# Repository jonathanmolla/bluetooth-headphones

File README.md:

# Bluetooth Headphones

Custom Bluetooth headphone electronics by **Jonathan Molla**, bringing together stereo audio circuit design, PCB layout, battery charging, STM32 controller configuration, and LTspice simulation.

## Main audio PCB

[Main audio PCB source](hardware/main/) · [Audio and controller schematics](docs/schematics/main/)

## Charging and power PCB

[Charging and power PCB source](hardware/power/) · [Charging circuit schematic](docs/schematics/power/Charging%20and%20Power.svg)

## Project at a glance

| Area | Implementation in this repository |
| --- | --- |
| Bluetooth audio | Microchip BM83 module in the KiCad audio schematic |
| Headphone amplifier | TI TPA6130A2, with AC-coupled analog inputs |
| Controller | STM32U031C8T6 firmware, BM83 UART, amplifier control, and battery monitoring |
| Charging | MCP73833 circuit on a separate power PCB |
| Battery / drivers | SparkFun PRT-13851 protected 400 mAh pack; Ole Wolff OWR-4009T-38E, nominal 38 ohm |
| BM83 programming | Separate single-PCB spring-contact fixture, revision C |
| Regulation | TPS7A2030PDBVR, fixed 3.0 V regulator |
| Design tools | KiCad, STM32CubeMX, LTspice |
| Simulation scope | Simplified analog coupling and voltage-gain models |

## Explore the project

| What you want to see | Where to find it |
| --- | --- |
| **PCB layouts and editable board files** | [Main audio PCB](hardware/main/#main-audio-pcb) · [Charging and power PCB](hardware/power/#charging-and-power-pcb) |
| **Schematics** | [Audio, controller, and charging circuit diagrams](docs/schematics/) |
| **Board images** | [Main audio and power board previews](docs/images/) |
| **Circuit design and component choices** | [Architecture and design decisions](docs/design.md) |
| **STM32 firmware** | [CubeIDE project, CubeMX configuration, and build instructions](firmware/) |
| **Audio simulation** | [LTspice circuit, models, and run instructions](simulation/) |
| **Component lists** | [Main audio board BOM](hardware/main/bom.csv) · [Power board BOM](hardware/power/bom.csv) |
| **Engineering checks** | [Schematic and PCB check results](docs/validation.md) |
| **Opening the design files** | [Software and setup guide](docs/getting-started.md) |
| **Design deliverables** | [Project file guide](docs/roadmap.md) |

## System architecture

```mermaid
flowchart LR
    BT[Bluetooth source] --> BM[BM83 module]
    BM --> AC[AC coupling]
    AC --> AMP[TPA6130A2 amplifier]
    AMP --> HP[Left and right headphone drivers]
    USB[USB power input] --> CHG[MCP73833 charging circuit]
    CHG <--> BAT[Single-cell battery]
    BAT --> RAIL[VBAT rail]
    RAIL --> BM
    RAIL --> AMP
    RAIL --> LDO[TPS7A20 3.0 V regulator]
    LDO --> MCU[STM32U031 controller]
    BTN[Buttons] --> MCU
    MCU -. control interfaces .-> BM
    MCU -. I2C control .-> AMP
```

This is an architectural overview. Exact connections and component values are defined by the native schematics. The main/audio board and charging/power board are separate KiCad projects.

## Engineering highlights

- Hierarchical schematic organization for audio and MCU controls.
- A separate charging and regulation PCB.
- Project-local symbols and footprints alongside the native KiCad files.
- Stereo AC-coupling analysis with parameterized input resistance, gain, and driver loads.
- STM32 pin and peripheral configuration captured in a reproducible `.ioc` file.
- Recorded KiCad electrical and design-rule checks with a structured measurement procedure.

## Repository layout

```text
hardware/
  main/          Main audio PCB, audio and controller schematics, local libraries
  power/         Charging and power PCB, schematic and local libraries
  programmer/    Single-PCB BM83 fixture, probe footprints and assembly instructions
firmware/        STM32CubeIDE project and CubeMX controller configuration
simulation/      LTspice audio circuit, symbols, models and instructions
docs/
  images/        PCB layout previews
  schematics/    Browser-readable schematic exports
  checks/        Recorded KiCad design checks
```

## Author and references

Project owner: [Jonathan Molla](https://github.com/jonathanmolla).

See [references and third-party materials](docs/references.md) for component sources and [reuse information](NOTICE.md) before reusing the files.

[BM83 programmer source and instructions](hardware/programmer/) · [Latest design review](docs/design-review-2026-11-14.md)

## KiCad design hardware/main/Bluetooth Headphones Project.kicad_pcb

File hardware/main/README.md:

# Main audio board

This board brings together BM83 Bluetooth audio, the TPA6130A2 headphone amplifier, and the STM32 controller and button circuitry.

## Main audio PCB

**Editable board layout:** [Bluetooth Headphones Project.kicad_pcb](Bluetooth%20Headphones%20Project.kicad_pcb)

**Open the complete KiCad project:** [Bluetooth Headphones Project.kicad_pro](Bluetooth%20Headphones%20Project.kicad_pro)

**View the layout in your browser:** [Main audio PCB preview](../../docs/images/main-board.svg)

## Schematics and component list

| File | Contents |
| --- | --- |
| [Root schematic](Bluetooth%20Headphones%20Project.kicad_sch) | Project hierarchy linking the audio and controller sheets |
| [Audio schematic](Bluetooth_Audio.kicad_sch) | BM83 module, AC coupling, TPA6130A2 amplifier and headphone outputs |
| [Controller schematic](MCU_Buttons.kicad_sch) | STM32 controller and button connections |
| [Component list](bom.csv) | Schematic references, values, footprints and datasheet links |

[View all schematic previews](../../docs/schematics/) · [Open the separate charging and power board](../power/)

## Library files

`Project_Audio.pretty/` and `STM32.pretty/` contain project-local footprints. The `.kicad_sym` files contain project-local symbols. Keep these folders and both library tables beside the project when downloading it.

## November 14 review

[Cross-board circuit and layout review](../../docs/design-review-2026-11-14.md) records component values, inter-board pinout, battery/driver selection and reference-design comparisons. The CSV lists schematic parts; the existing Google document remains the purchasing BOM.

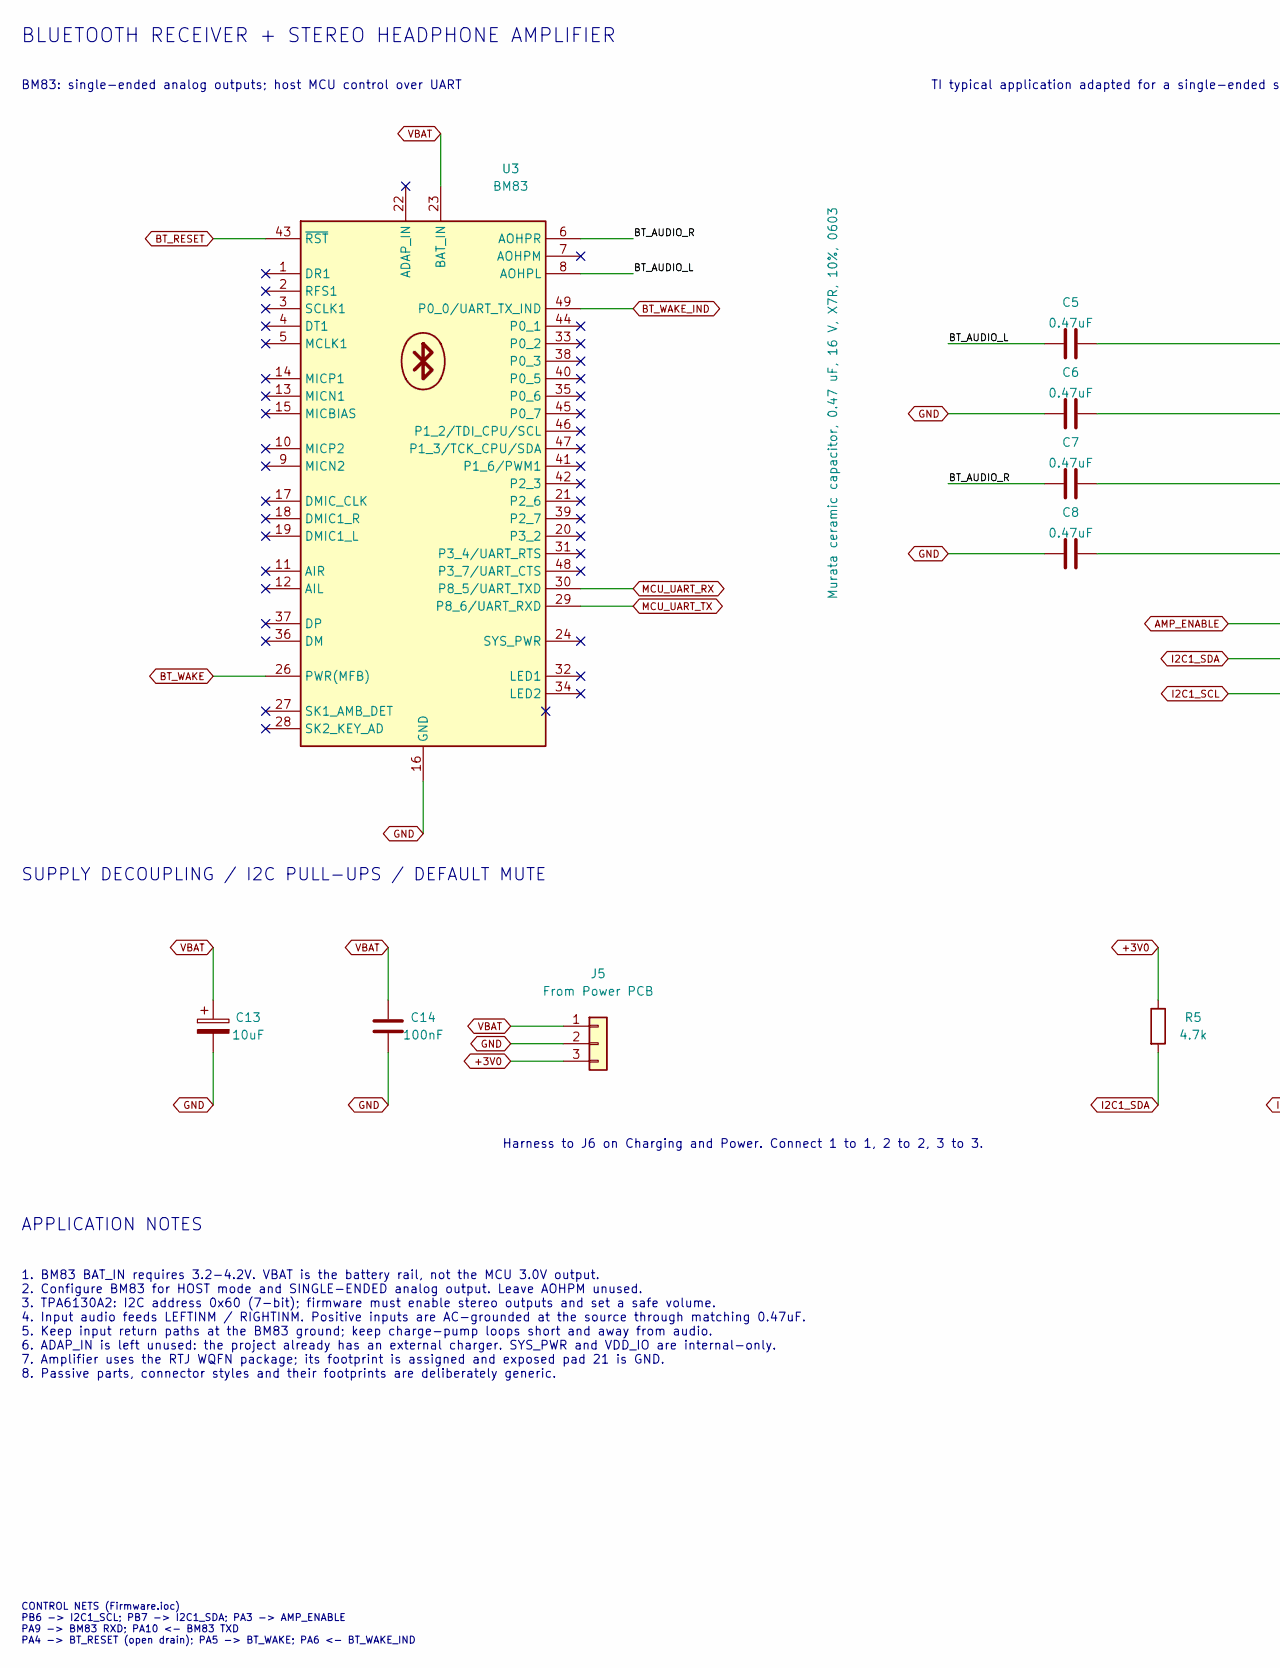
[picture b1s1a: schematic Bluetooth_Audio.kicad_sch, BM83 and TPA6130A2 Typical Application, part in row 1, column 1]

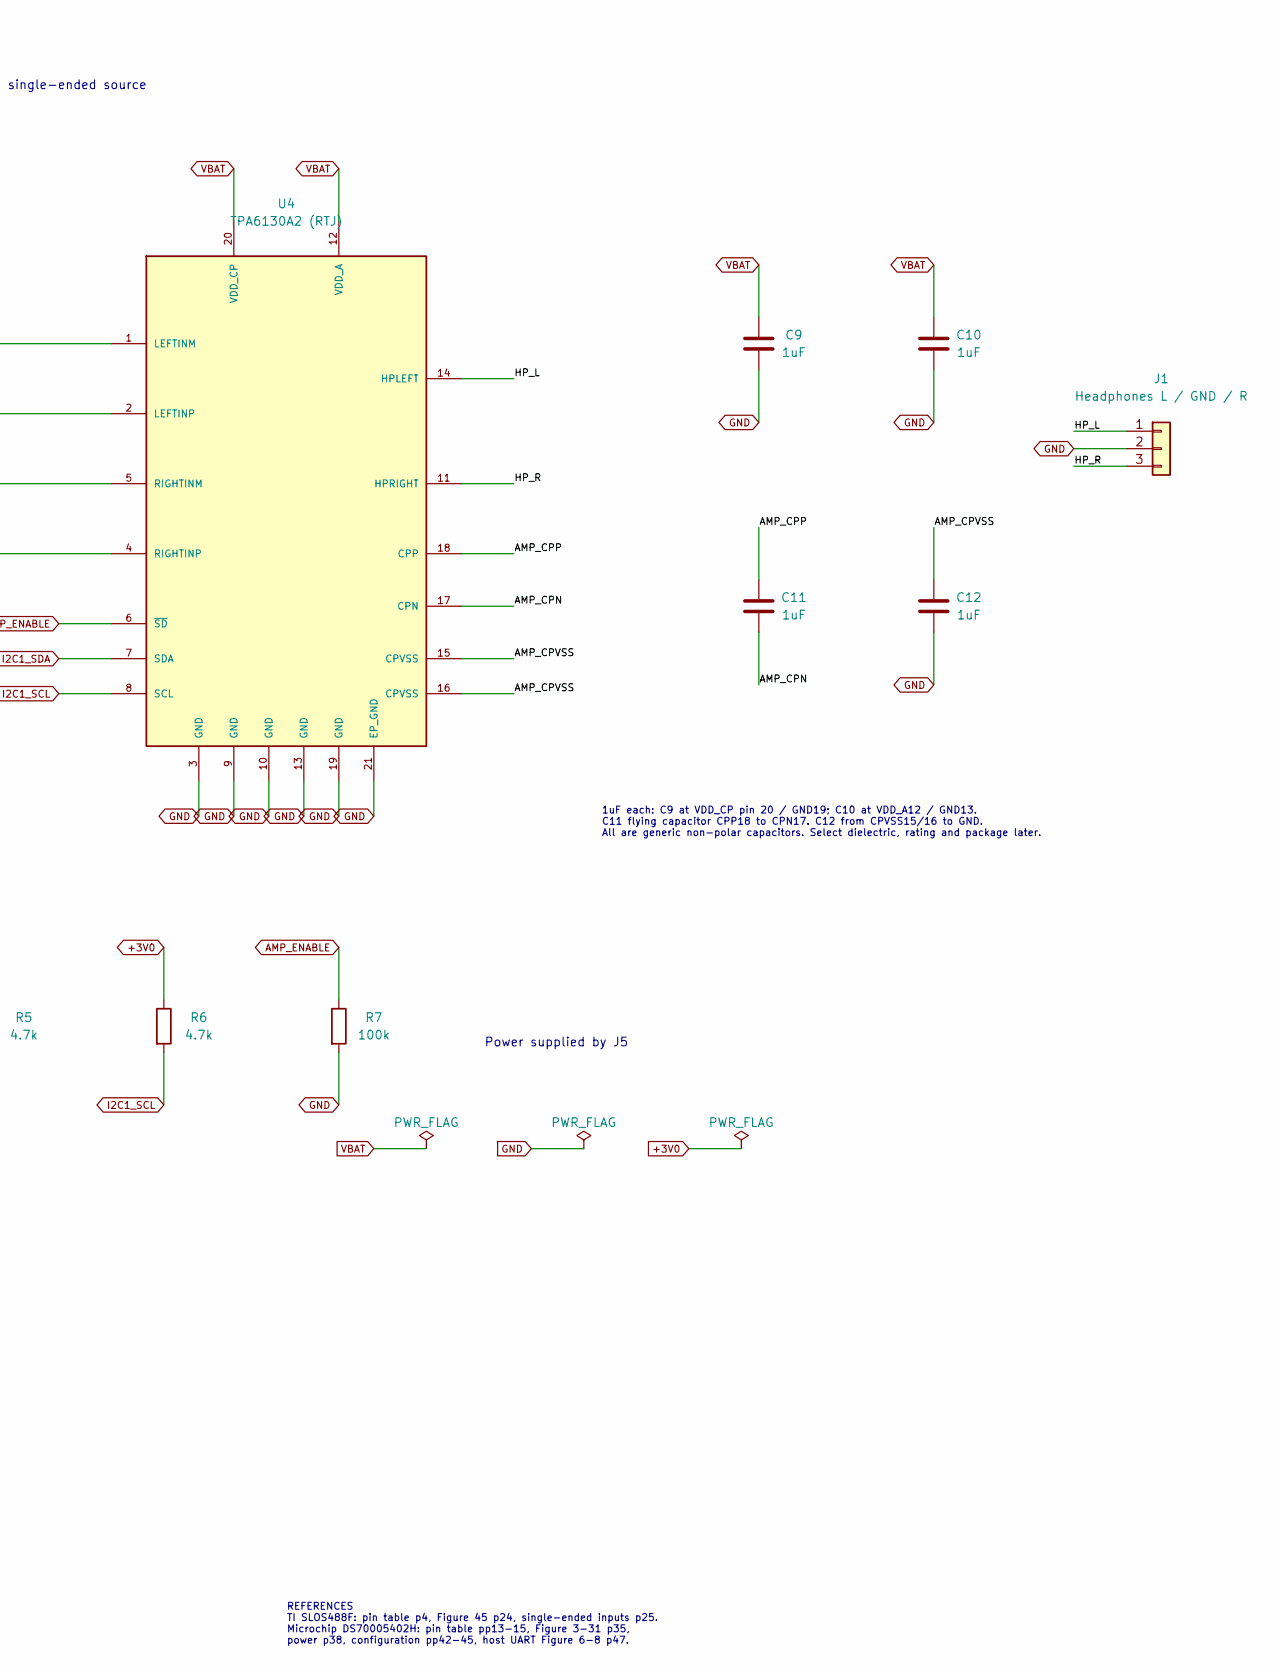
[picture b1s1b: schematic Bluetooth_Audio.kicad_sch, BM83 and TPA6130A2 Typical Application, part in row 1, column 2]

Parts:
C5, C6, C7, C8: 0.47uF; C_0603_1608Metric; MPN GRM188R71C474KA88D
C9, C10, C11, C12: 1uF; C_0805_2012Metric; MPN GRM219R71E105KA88D
C13: 10uF; CP_Elec_4x5.8; MPN EEE-FN1C100R
C14: 100nF; C_0603_1608Metric; MPN GRM188R72A104KA35J
J1: Headphones L / GND / R; PinHeader_1x03_P2.54mm_Vertical; MPN TSW-103-07-G-S
J5: From Power PCB; JST_PH_B3B-PH-K_1x03_P2.00mm_Vertical; MPN B3B-PH-K-S(LF)(SN)
R5, R6: 4.7k; R_0603_1608Metric; MPN RC0603FR-074K7L
R7: 100k; R_0603_1608Metric; MPN RC0603FR-07100KL
U3: BM83; Microchip_BM83
U4: TPA6130A2 (RTJ); TPA6130A2_RTJ_4x4mm_P0.5mm_EP2.7x2.7mm

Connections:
+3V0: J5.3, R5.1, R6.1; also elsewhere on the board
/Bluetooth_and_Audio/AMP_CPN: C11.2, U4.17 (CPN)
/Bluetooth_and_Audio/AMP_CPP: C11.1, U4.18 (CPP)
/Bluetooth_and_Audio/AMP_CPVSS: C12.1, U4.15 (CPVSS), U4.16 (CPVSS)
/Bluetooth_and_Audio/BT_AUDIO_L: C5.2, U3.8 (AOHPL)
/Bluetooth_and_Audio/BT_AUDIO_R: C7.2, U3.6 (AOHPR)
/Bluetooth_and_Audio/HP_L: J1.1, U4.14 (HPLEFT)
/Bluetooth_and_Audio/HP_R: J1.3, U4.11 (HPRIGHT)
AMP_ENABLE: R7.1, U4.6 (~SD); also elsewhere on the board
BT_RESET: U3.43 (~RST); also elsewhere on the board
BT_WAKE: U3.26 (PWR(MFB)); also elsewhere on the board
BT_WAKE_IND: U3.49 (P0_0/UART_TX_IND); also elsewhere on the board
GND: C6.2, C8.2, C9.2, C10.2, C12.2, C13.2, C14.2, J1.2, J5.2, R7.2, U3.16 (GND), U3.50 (GND), U3.56 (GND), U3.57 (GND), U4.3 (GND), U4.9 (GND), U4.10 (GND), U4.13 (GND), U4.19 (GND), U4.21 (EP_GND); also elsewhere on the board
I2C1_SCL: R6.2, U4.8 (SCL); also elsewhere on the board
I2C1_SDA: R5.2, U4.7 (SDA); also elsewhere on the board
MCU_UART_RX: U3.30 (P8_5/UART_TXD); also elsewhere on the board
MCU_UART_TX: U3.29 (P8_6/UART_RXD); also elsewhere on the board
unnamed: C5.1, U4.1 (LEFTINM)
unnamed: C6.1, U4.2 (LEFTINP)
unnamed: C7.1, U4.5 (RIGHTINM)
unnamed: C8.1, U4.4 (RIGHTINP)
VBAT: C9.1, C10.1, C13.1, C14.1, J5.1, U3.23 (BAT_IN), U4.12 (VDD_A), U4.20 (VDD_CP); also elsewhere on the board

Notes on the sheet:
SUPPLY DECOUPLING / I2C PULL-UPS / DEFAULT MUTE
REFERENCES TI SLOS488F: pin table p4, Figure 45 p24, single-ended inputs p25. Microchip DS70005402H: pin table pp13-15, Figure 3-31 p35, power p38, configuration pp42-45, host UART Figure 6-8 p47.
1uF each: C9 at VDD_CP pin 20 / GND19; C10 at VDD_A12 / GND13. C11 flying capacitor CPP18 to CPN17. C12 from CPVSS15/16 to GND. All are generic non-polar capacitors. Select dielectric, rating and package later.
CONTROL NETS (Firmware.ioc) PB6 -> I2C1_SCL; PB7 -> I2C1_SDA; PA3 -> AMP_ENABLE PA9 -> BM83 RXD; PA10 <- BM83 TXD PA4 -> BT_RESET (open drain); PA5 -> BT_WAKE; PA6 <- BT_WAKE_IND
1. BM83 BAT_IN requires 3.2-4.2V. VBAT is the battery rail, not the MCU 3.0V output. 2. Configure BM83 for HOST mode and SINGLE-ENDED analog output. Leave AOHPM unused. 3. TPA6130A2: I2C address 0x60 (7-bit); firmware must enable stereo outputs and set a safe volume. 4. Input audio feeds LEFTINM / 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
Harness to J6 on Charging and Power. Connect 1 to 1, 2 to 2, 3 to 3.
APPLICATION NOTES
TI typical application adapted for a single-ended source
BLUETOOTH RECEIVER + STEREO HEADPHONE AMPLIFIER
BM83: single-ended analog outputs; host MCU control over UART
Power supplied by J5

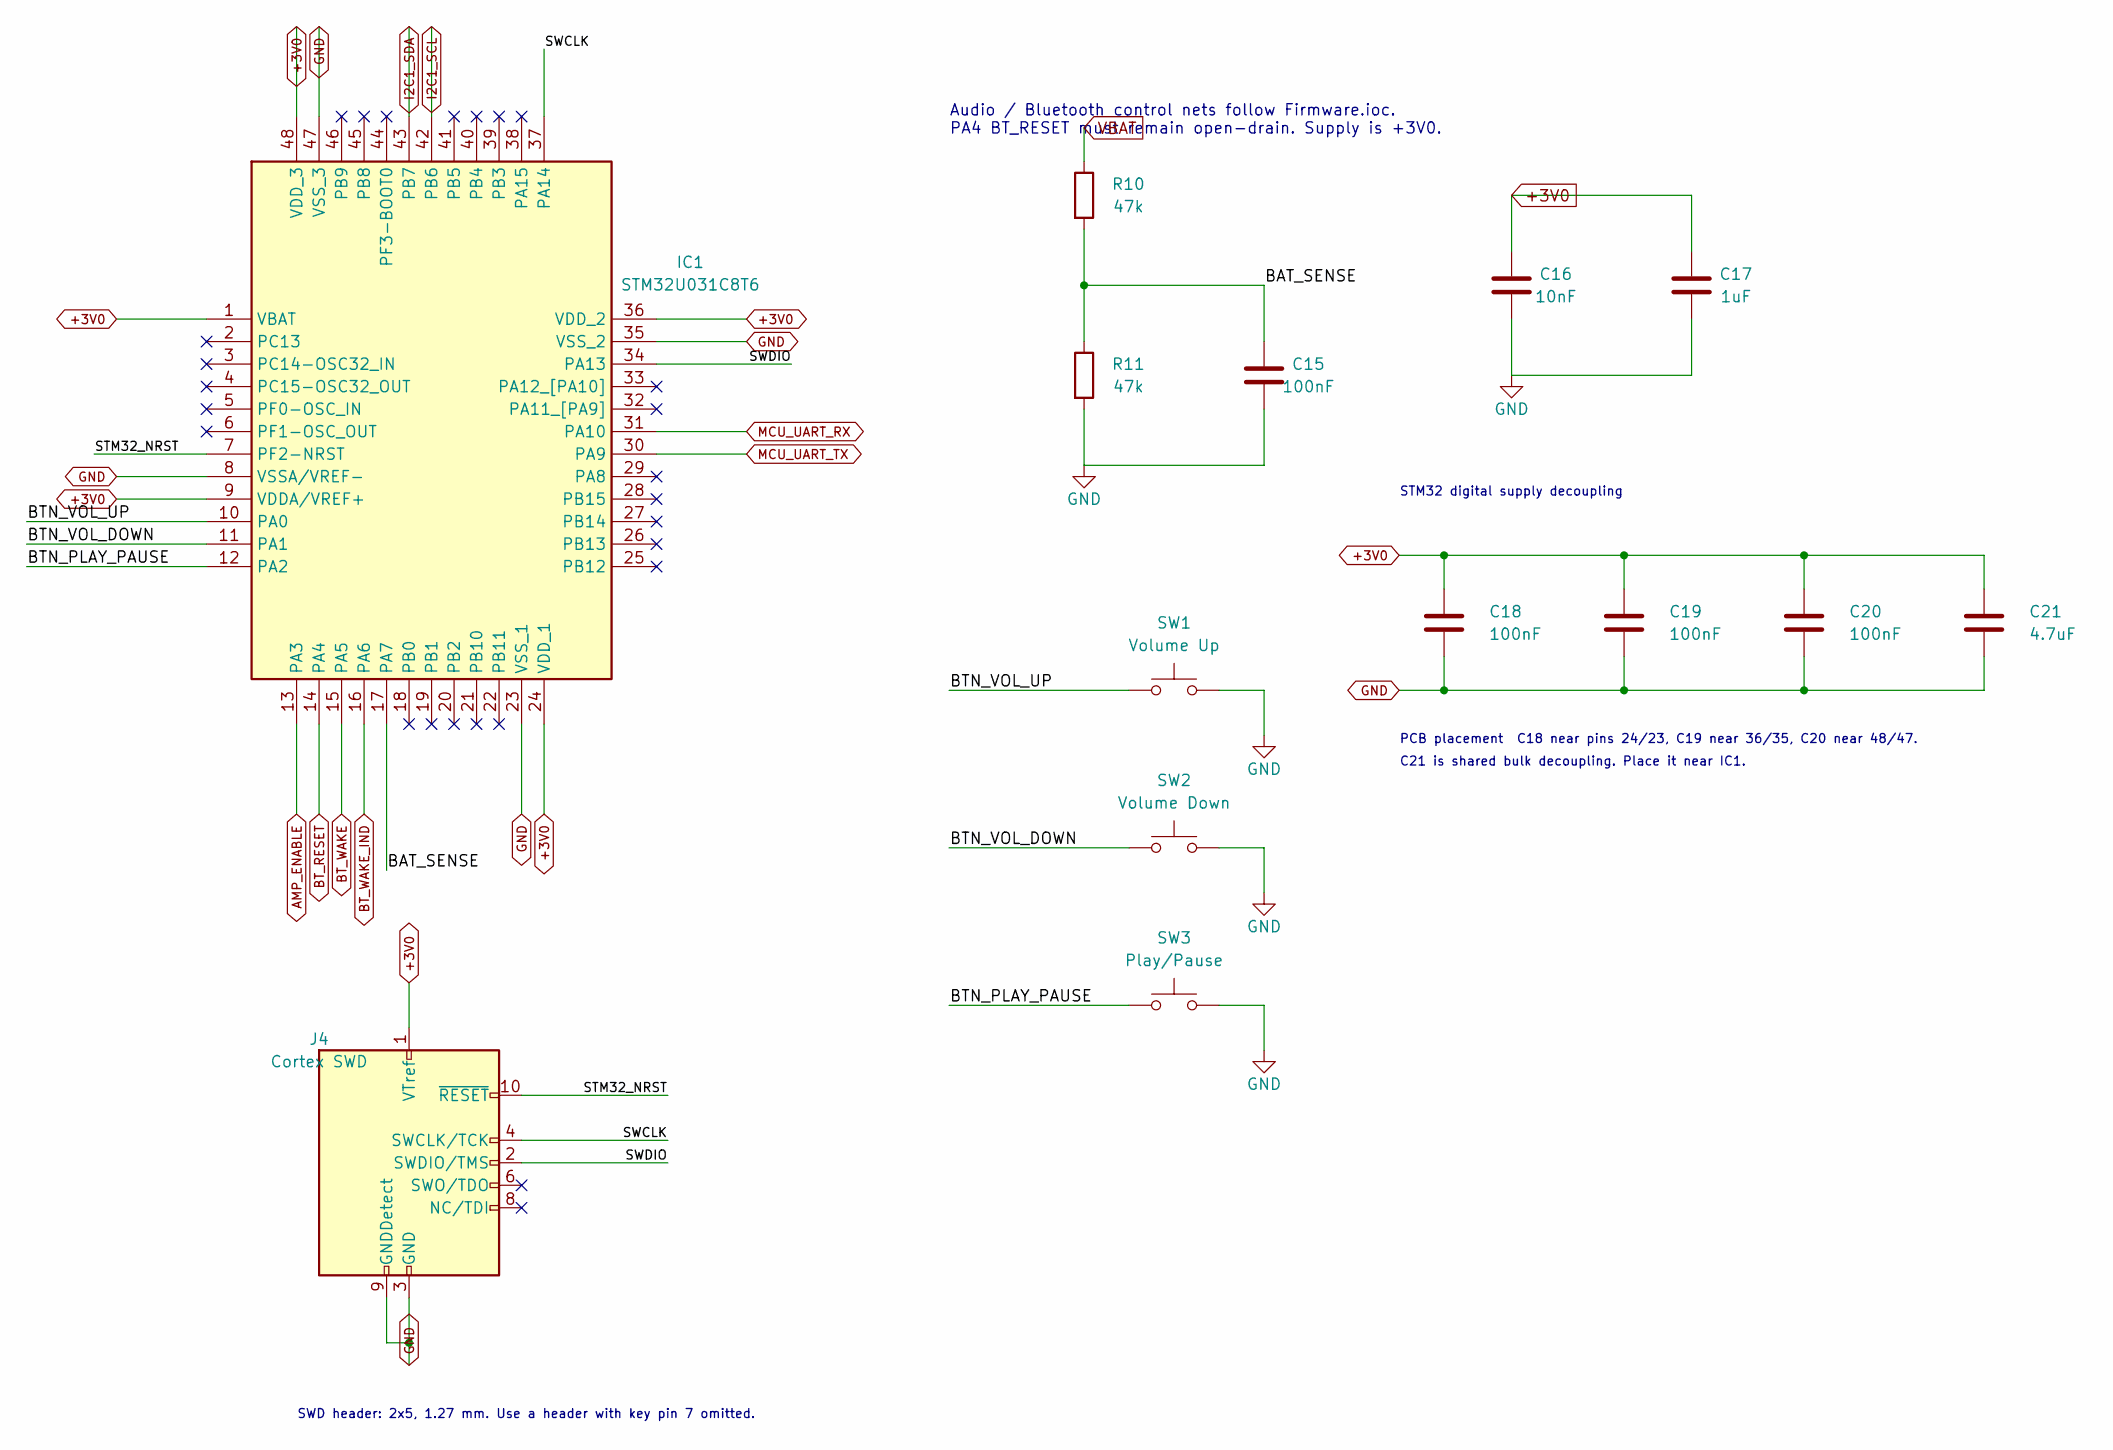
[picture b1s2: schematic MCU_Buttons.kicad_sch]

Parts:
C15: 100nF; C_0603_1608Metric; MPN GRM188R72A104KA35J
C16: 10nF; C_0603_1608Metric; MPN CC0603KRX7R9BB103
C17: 1uF; C_0805_2012Metric; MPN GRM219R71E105KA88D
C18, C19, C20: 100nF; C_0603_1608Metric
C21: 4.7uF; C_0805_2012Metric
IC1: STM32U031C8T6; QFP50P900X900X160-48N; Manufacturer_Part_Number STM32U031C8T6; Mouser Part Number 511-STM32U031C8T6
J4: Cortex SWD; PinHeader_2x05_P1.27mm_Vertical
R10, R11: 47k; R_0603_1608Metric; MPN RC0603FR-0747KL
SW1: Volume Up; SW_TH_Tactile_Omron_B3F-100x; MPN B3F-1002-G
SW2: Volume Down; SW_TH_Tactile_Omron_B3F-100x; MPN B3F-1002-G
SW3: Play/Pause; SW_TH_Tactile_Omron_B3F-100x; MPN B3F-1002-G

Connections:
+3V0: C16.1, C17.1, C18.1, C19.1, C20.1, C21.1, IC1.1 (VBAT), IC1.9 (VDDA/VREF+), IC1.24 (VDD_1), IC1.36 (VDD_2), IC1.48 (VDD_3), J4.1 (VTref); also elsewhere on the board
/MCU_and_Buttons/BAT_SENSE: C15.1, IC1.17 (PA7), R10.2, R11.1
/MCU_and_Buttons/BTN_PLAY_PAUSE: IC1.12 (PA2), SW3.1
/MCU_and_Buttons/BTN_VOL_DOWN: IC1.11 (PA1), SW2.1
/MCU_and_Buttons/BTN_VOL_UP: IC1.10 (PA0), SW1.1
/MCU_and_Buttons/STM32_NRST: IC1.7 (PF2-NRST), J4.10 (~RESET)
/MCU_and_Buttons/SWCLK: IC1.37 (PA14), J4.4 (SWCLK/TCK)
/MCU_and_Buttons/SWDIO: IC1.34 (PA13), J4.2 (SWDIO/TMS)
AMP_ENABLE: IC1.13 (PA3); also elsewhere on the board
BT_RESET: IC1.14 (PA4); also elsewhere on the board
BT_WAKE: IC1.15 (PA5); also elsewhere on the board
BT_WAKE_IND: IC1.16 (PA6); also elsewhere on the board
GND: C15.2, C16.2, C17.2, C18.2, C19.2, C20.2, C21.2, IC1.8 (VSSA/VREF-), IC1.23 (VSS_1), IC1.35 (VSS_2), IC1.47 (VSS_3), J4.3 (GND), J4.5 (GND), J4.9 (GNDDetect), R11.2, SW1.2, SW2.2, SW3.2; also elsewhere on the board
I2C1_SCL: IC1.42 (PB6); also elsewhere on the board
I2C1_SDA: IC1.43 (PB7); also elsewhere on the board
MCU_UART_RX: IC1.31 (PA10); also elsewhere on the board
MCU_UART_TX: IC1.30 (PA9); also elsewhere on the board
VBAT: R10.1; also elsewhere on the board

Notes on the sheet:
C21 is shared bulk decoupling. Place it near IC1.
Audio / Bluetooth control nets follow Firmware.ioc. PA4 BT_RESET must remain open-drain. Supply is +3V0.
STM32 digital supply decoupling
SWD header: 2x5, 1.27 mm. Use a header with key pin 7 omitted.
PCB placement C18 near pins 24/23, C19 near 36/35, C20 near 48/47.

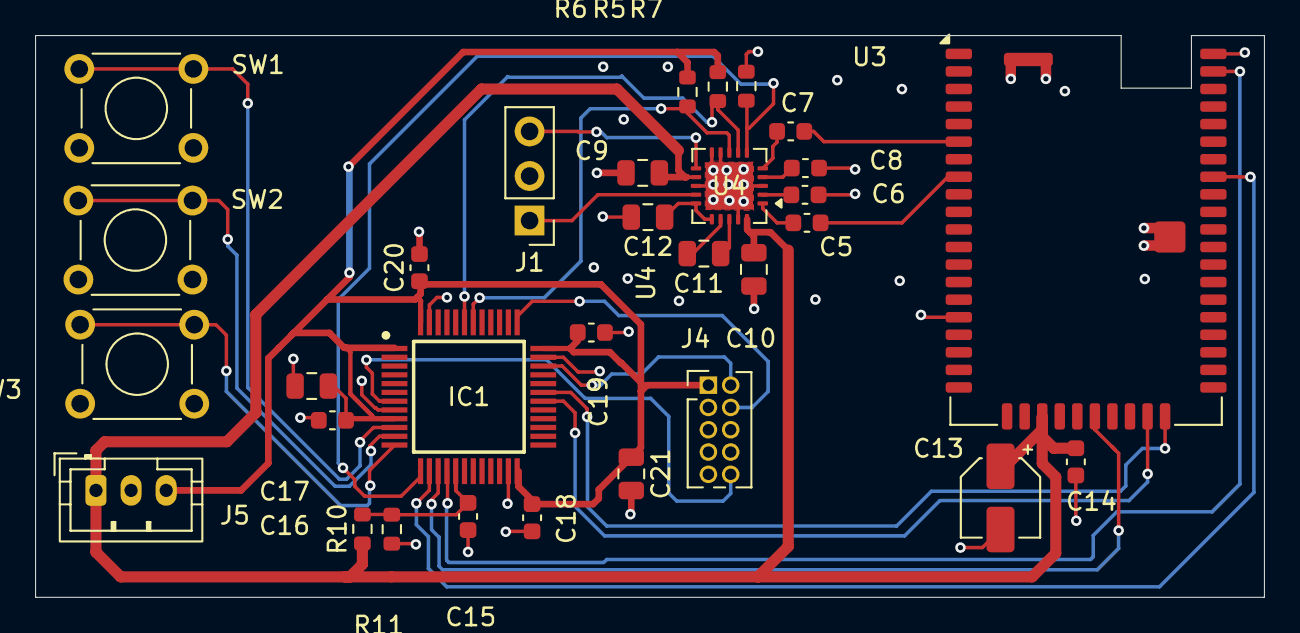
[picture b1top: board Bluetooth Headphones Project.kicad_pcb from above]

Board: 4 copper layers, 70.0 x 32.0 mm, 31 parts (0 on the bottom side), 29 nets.

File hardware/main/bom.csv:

Reference,Value,Footprint,Datasheet,Status
C15,100nF,Capacitor_SMD:C_0603_1608Metric,,Saved schematic value; see review for pending recommendations
C16,10nF,Capacitor_SMD:C_0603_1608Metric,,Saved schematic value; see review for pending recommendations
C17,1uF,Capacitor_SMD:C_0805_2012Metric,,Saved schematic value; see review for pending recommendations
C18,100nF,Capacitor_SMD:C_0603_1608Metric,,Saved schematic value; see review for pending recommendations
C19,100nF,Capacitor_SMD:C_0603_1608Metric,,Saved schematic value; see review for pending recommendations
C20,100nF,Capacitor_SMD:C_0603_1608Metric,,Saved schematic value; see review for pending recommendations
C21,4.7uF,Capacitor_SMD:C_0805_2012Metric,,Saved schematic value; see review for pending recommendations
IC1,STM32U031C8T6,STM32:QFP50P900X900X160-48N,https://www.st.com/resource/en/datasheet/stm32u031f4.pdf,Saved schematic value; see review for pending recommendations
J4,Cortex SWD,Connector_PinHeader_1.27mm:PinHeader_2x05_P1.27mm_Vertical,,Saved schematic value; see review for pending recommendations
R10,47k,Resistor_SMD:R_0603_1608Metric,,Saved schematic value; see review for pending recommendations
R11,47k,Resistor_SMD:R_0603_1608Metric,,Saved schematic value; see review for pending recommendations
SW1,Volume Up,Button_Switch_THT:SW_TH_Tactile_Omron_B3F-100x,,Saved schematic value; see review for pending recommendations
SW2,Volume Down,Button_Switch_THT:SW_TH_Tactile_Omron_B3F-100x,,Saved schematic value; see review for pending recommendations
SW3,Play/Pause,Button_Switch_THT:SW_TH_Tactile_Omron_B3F-100x,,Saved schematic value; see review for pending recommendations
C5,0.47uF,Capacitor_SMD:C_0603_1608Metric,,Saved schematic value; see review for pending recommendations
C6,0.47uF,Capacitor_SMD:C_0603_1608Metric,,Saved schematic value; see review for pending recommendations
C7,0.47uF,Capacitor_SMD:C_0603_1608Metric,,Saved schematic value; see review for pending recommendations
C8,0.47uF,Capacitor_SMD:C_0603_1608Metric,,Saved schematic value; see review for pending recommendations
C9,1uF,Capacitor_SMD:C_0805_2012Metric,,Saved schematic value; see review for pending recommendations
C10,1uF,Capacitor_SMD:C_0805_2012Metric,,Saved schematic value; see review for pending recommendations
C11,1uF,Capacitor_SMD:C_0805_2012Metric,,Saved schematic value; see review for pending recommendations
C12,1uF,Capacitor_SMD:C_0805_2012Metric,,Saved schematic value; see review for pending recommendations
C13,10uF,Capacitor_SMD:CP_Elec_4x5.8,,Saved schematic value; see review for pending recommendations
C14,100nF,Capacitor_SMD:C_0603_1608Metric,,Saved schematic value; see review for pending recommendations
J1,Headphones L / GND / R,Connector_PinHeader_2.54mm:PinHeader_1x03_P2.54mm_Vertical,,Saved schematic value; see review for pending recommendations
J5,From Power PCB,Connector_JST:JST_PH_B3B-PH-K_1x03_P2.00mm_Vertical,,Saved schematic value; see review for pending recommendations
R5,4.7k,Resistor_SMD:R_0603_1608Metric,,Saved schematic value; see review for pending recommendations
R6,4.7k,Resistor_SMD:R_0603_1608Metric,,Saved schematic value; see review for pending recommendations
R7,100k,Resistor_SMD:R_0603_1608Metric,,Saved schematic value; see review for pending recommendations
U3,BM83,RF_Module:Microchip_BM83,,Saved schematic value; see review for pending recommendations
U4,TPA6130A2 (RTJ),Project_Audio:TPA6130A2_RTJ_4x4mm_P0.5mm_EP2.7x2.7mm,,Saved schematic value; see review for pending recommendations

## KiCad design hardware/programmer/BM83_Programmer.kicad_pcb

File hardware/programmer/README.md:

# BM83 programmer — revision C

One PCB with ten direct spring contacts for configuring a loose BM83 module before main-board assembly.

- [KiCad project](BM83_Programmer.kicad_pro), [schematic](BM83_Programmer.kicad_sch), [PCB](BM83_Programmer.kicad_pcb)
- [Assembly, pin mapping and manufacturer references](Instructions/Assembly%20and%20Pin%20Mapping.md)
- [Locator and clamp CAD](Instructions/Fixture.scad)
- [Schematic component list](bom.csv)
- [Layout preview](../../docs/images/programmer-board.svg)
- [Schematic preview](../../docs/schematics/programmer/BM83_Programmer.svg)
- [Design calculations and fixture geometry](../../docs/design-review-2026-11-14.md#programmer-revision-c)

J1: 1 +5V, 2 GND, 3 adapter TX to BM83 RX, 4 adapter RX from BM83 TX. UART logic must be 3.3 V. JP2 grounds TEST; SW1 resets. BAT_IN has a capacitor only and must not receive USB 5 V.

The fixture combines PCB routing, a probe-collar support and screw-down clamp bars. The assembly procedure defines probe alignment, contact continuity and module programming.

The CSV is schematic-derived and excludes mechanical parts and external equipment. The existing Google document remains the purchasing BOM. Manufacturer documents are linked in the instructions rather than redistributed here.

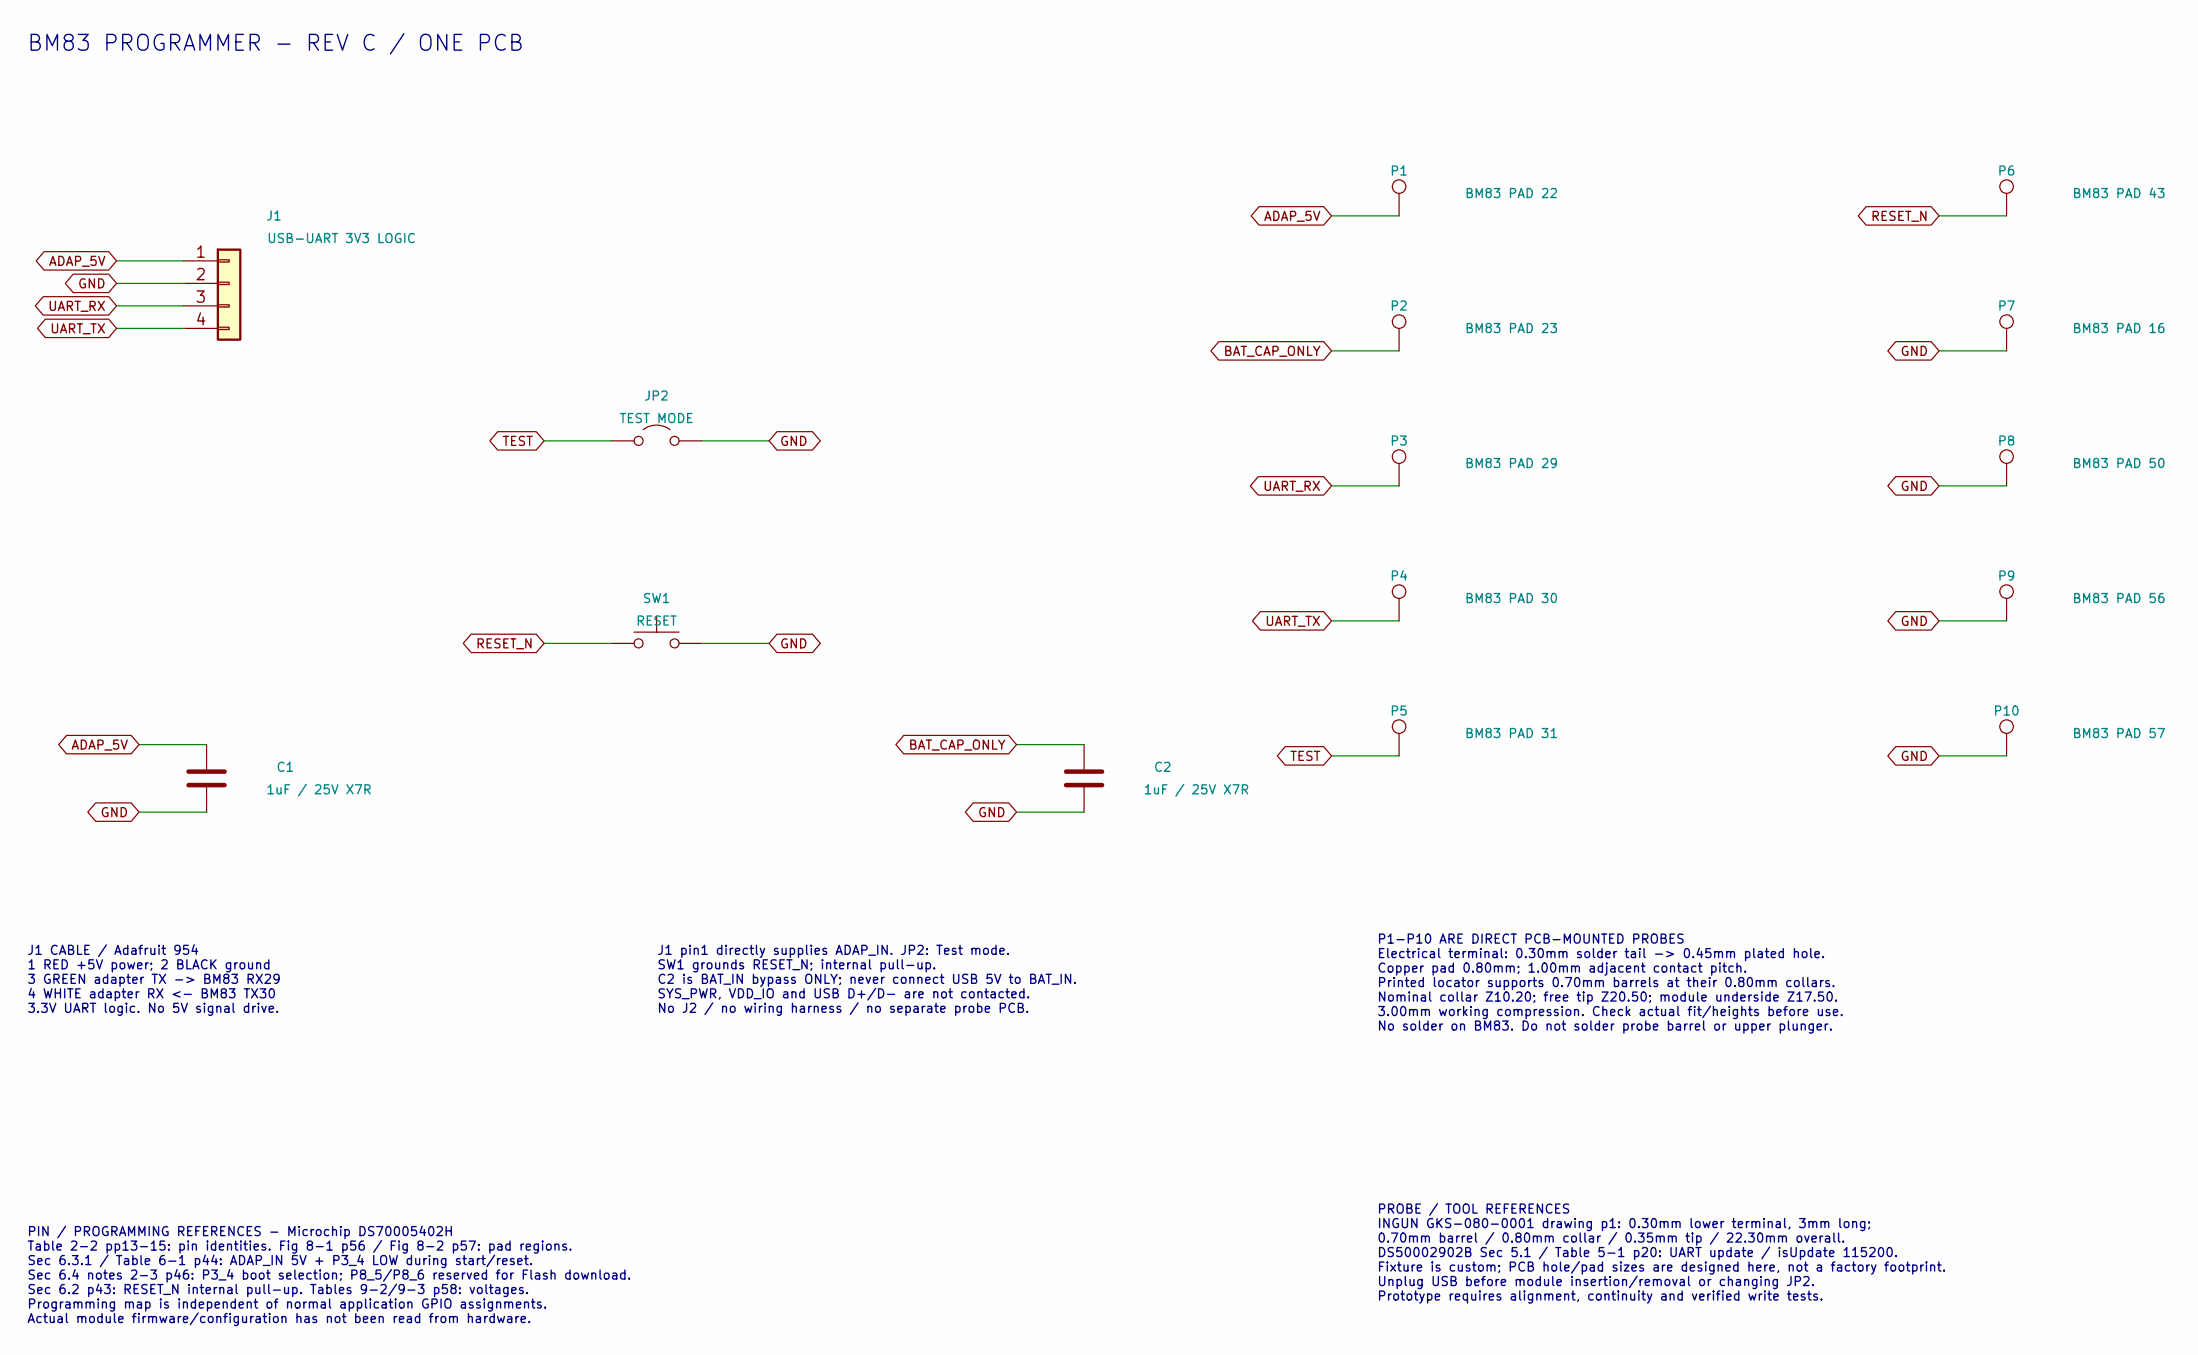
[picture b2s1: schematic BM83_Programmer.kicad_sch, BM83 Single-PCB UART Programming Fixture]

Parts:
C1, C2: 1uF / 25V X7R; C_0805_2012Metric; MPN GRM219R71E105KA88D
J1: USB-UART 3V3 LOGIC; PinHeader_1x04_P2.54mm_Vertical; MPN TSW-104-07-G-S
JP2: TEST MODE; PinHeader_1x02_P2.54mm_Vertical; MPN TSW-102-07-G-S
P1: BM83 PAD 22; TestPoint_INGUN_GKS080_SolderTail; MPN GKS-080-0001
P2: BM83 PAD 23; TestPoint_INGUN_GKS080_SolderTail; MPN GKS-080-0001
P3: BM83 PAD 29; TestPoint_INGUN_GKS080_SolderTail; MPN GKS-080-0001
P4: BM83 PAD 30; TestPoint_INGUN_GKS080_SolderTail; MPN GKS-080-0001
P5: BM83 PAD 31; TestPoint_INGUN_GKS080_SolderTail; MPN GKS-080-0001
P6: BM83 PAD 43; TestPoint_INGUN_GKS080_SolderTail; MPN GKS-080-0001
P7: BM83 PAD 16; TestPoint_INGUN_GKS080_SolderTail; MPN GKS-080-0001
P8: BM83 PAD 50; TestPoint_INGUN_GKS080_SolderTail; MPN GKS-080-0001
P9: BM83 PAD 56; TestPoint_INGUN_GKS080_SolderTail; MPN GKS-080-0001
P10: BM83 PAD 57; TestPoint_INGUN_GKS080_SolderTail; MPN GKS-080-0001
SW1: RESET; SW_PUSH_6mm; MPN B3F-1000

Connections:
ADAP_5V: C1.1, J1.1, P1.1
BAT_CAP_ONLY: C2.1, P2.1
GND: C1.2, C2.2, J1.2, JP2.2 (B), P7.1, P8.1, P9.1, P10.1, SW1.2
RESET_N: P6.1, SW1.1
TEST: JP2.1 (A), P5.1
UART_RX: J1.3, P3.1
UART_TX: J1.4, P4.1

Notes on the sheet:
BM83 PROGRAMMER - REV C / ONE PCB
J1 CABLE / Adafruit 954 1 RED +5V power; 2 BLACK ground 3 GREEN adapter TX -> BM83 RX29 4 WHITE adapter RX <- BM83 TX30 3.3V UART logic. No 5V signal drive.
J1 pin1 directly supplies ADAP_IN. JP2: Test mode. SW1 grounds RESET_N; internal pull-up. C2 is BAT_IN bypass ONLY; never connect USB 5V to BAT_IN. SYS_PWR, VDD_IO and USB D+/D- are not contacted. No J2 / no wiring harness / no separate probe PCB.
P1-P10 ARE DIRECT PCB-MOUNTED PROBES Electrical terminal: 0.30mm solder tail -> 0.45mm plated hole. Copper pad 0.80mm; 1.00mm adjacent contact pitch. Printed locator supports 0.70mm barrels at their 0.80mm collars. Nominal collar Z10.20; free tip Z20.50; module underside Z17.50. 3.00mm working comp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
PIN / PROGRAMMING REFERENCES - Microchip DS70005402H Table 2-2 pp13-15: pin identities. Fig 8-1 p56 / Fig 8-2 p57: pad regions. Sec 6.3.1 / Table 6-1 p44: ADAP_IN 5V + P3_4 LOW during start/reset. Sec 6.4 notes 2-3 p46: P3_4 boot selection; P8_5/P8_6 reserved for Flash download. Sec 6.2 p43: RESET_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
PROBE / TOOL REFERENCES INGUN GKS-080-0001 drawing p1: 0.30mm lower terminal, 3mm long; 0.70mm barrel / 0.80mm collar / 0.35mm tip / 22.30mm overall. DS50002902B Sec 5.1 / Table 5-1 p20: UART update / isUpdate 115200. Fixture is custom; PCB hole/pad sizes are designed here, not a factory footprint.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
